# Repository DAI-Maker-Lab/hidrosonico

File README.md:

# Hidrosónico
<i>Hidrosónico</i> is a stream gauge using a <a href="http://www.maxbotix.com/documents/HRXL-MaxSonar-WR_Datasheet.pdf">MaxSonar HRXL MB7369</a> sonar rangefinder, a <a href="http://www.seeedstudio.com/wiki/Seeeduino-Stalker_v3">Seeeduino Stalker v3</a> Arduino-compatible microcontroller platform, and an <a href="https://learn.adafruit.com/adafruit-fona-mini-gsm-gprs-cellular-phone-module/overview">Adafruit FONA 800</a> GSM module. It reads the distance between the sensor (specifically from where the housing meets the threading) and the water's surface directly below and sends this data at specified intervals to cloud-based storage, SMS, and/or email as determined by the user. It was designed to aid in collection of hydrological data and for flood early warning in developing countries. This version integrates a rain gauge at the request of the recipient. 

The code provided sends data to data.sparkfun.com as the cloud service but it could be easily adapted to any other provider. Please note the places in the code that are marked for user-specific input.

This is a beta unit and we will be making changes as a result of the data and experiences we are collecting from pilot installations in Honduras, as well as feedback from on-the-ground partners like CODEM-DC in Tegucigalpa.

All code and hardware files are being made available under open source licensing. If you use it, please let us know (robert_ryan-silva[at]dai.com), and if you improve it, please share!

##Bill of Materials

Links to vendors are provided for convenience and not meant to imply an endorsement of that vendor; most of the items are available from other sources, and most components can be adequately substituted with equivalents. We have no connections nor receive any benefit from any of the vendors indicated.

###Required:
<ul>
<li><b><a href="http://www.seeedstudio.com/depot/Seeeduino-Stalker-v3-p-1882.html?cPath=6_7">Seeeduino Stalker v3</a></b>. Most Arduino-compatible microcontrollers will work, but most will require additional circuitry to charge the battery from a solar cell and for use of the real-time clock. Some Arduino-compatibles will require some pin changes (though the Arduino Uno and its equivalents should be fine).</li>
<li><b><a href="https://www.adafruit.com/products/1946">Adafruit FONA 800</a> and <a href="https://www.adafruit.com/products/1859">antenna</a></b>. The FONA 808 would also work, but would require some wiring changes and would not fit on the circuit board as designed. Any GSM module that is not based on the SIMCOM SIM 800 series chips would need code changes to work properly.</li>
<li><b><a href="http://www.amazon.com/Maxbotix-MB7369-HRXL-MaxSonar-WRM/dp/B00A7YHBT2/ref=sr_1_1?ie=UTF8&qid=1434393383&sr=8-1&keywords=Maxbotix+MaxSonar+HRXL+MB7369&pebp=1434393385707&perid=1H5KG4AJ9JRJ434Q8SGC">Maxbotix MaxSonar HRXL MB7369</a></b>.</li>
<li><b>A solar panel</b>. We use <a href="https://www.adafruit.com/products/500">these</a>. We have not found any panels that terminate in the JST connector that the Stalker takes, so a <a href="https://www.adafruit.com/products/261">JST connector</a> is highly recommended; <a href="http://www.amazon.com/gp/product/B0076AY6J8?psc=1&redirect=true&ref_=oh_aui_search_detailpage">Scotchlok butt connectors</a> or similar (inside the enclosure, of course) make connecting the JST connector to the solar panel quite easy.</li>
<li><b>A lithium-ion battery</b>. We use <a href="https://www.adafruit.com/products/1781">these</a>.</li>
</ul>

###Optional:
<ul>
<li><b>Rain gauge</b>. You can collect rainfall data at the same site for a minimal additional cost with the addition of a rain gauge. The <i>Hidrosónico</i> code in the repository records data from a simple <a href="https://www.argentdata.com/catalog/product_info.php?products_id=168">Argent Data Systems rain gauge</a>. You'll need two 1K ohm resistors and a pair of 1N148 diodes to wire it to the microcontroller; an RJ-11 jack <a href="https://www.sparkfun.com/products/132">like this one from Sparkfun</a> will make this easier to work with, but you could strip the wires and solder them directly.</li>
<li><b>Circuit board</b>. Eagle files for a custom circuit board to accommodate the FONA and the optional rain gauge are included in the repository. You could cut this on a CNC machine or have it fabricated by a vendor like <a href="https://oshpark.com/">OSH Park</a>. It isn't strictly necessary -- you could wire the FONA directly -- but we found in practice that installation can be a violent process and connections coming loose is a real possibility. It is recommended especially if you intend to implement the rain gauge.</li>
<li><b>Interior structure</b>. The repository includes a STL file for an interior frame to hold the various internal components stable inside a 4 x 4 x 2 inch PVC junction box <a href=http://www.homedepot.com/p/Carlon-4-in-x-4-in-x-2-in-PVC-Junction-Box-5-Pack-E989NNJ-CAR/202206114">like this one</a>. We cut a 1-inch hole in the faceplate of the junction box and use PVC cement to attach a threaded 3/4-inch coupling <a href="http://www.homedepot.com/p/Carlon-3-4-in-PVC-Coupling-E940E-CTN/100404040">like this one</a>. Again, it's not necessary, but it does keep things from banging around much during installation. Additional holes must be drilled to accommodate the solar panel and the rain gauge. We use plumber's putty to fill the gaps around the cabling.</li>
<li><b>Mounts</b>. You'll want to mount the solar panel and optional rain gauge somehow. The repository includes SVG files for mounts that we have used with the PVC junction boxes. We cut these from sheet metal using waterjet cutters or 3.5mm polypropylene using laser cutters; both have the advantage of being easily bendable (with heat, in the case of polypropylene) to the desired angle. For those without access to fancy CNC cutters, the repository also includes a template for a simpler sheet metal solar panel mount that could be cut with aviation shears or other sheet metal cutting implements.</li>
<li><b><a href="http://www.seeedstudio.com/depot/Grove-4-pin-Female-Jumper-to-Grove-4-pin-Conversion-Cable-5-PCs-per-PAck-p-1020.html?cPath=98_106_57">Grove <-> female jumper cable</a></b>. Makes connecting the MaxBotix to the Stalker very easy indeed.</li>
<li><b>An Xbee 802.15.4 radio</b> will allow you to reprogram the unit from nearby without physically opening the housing, which can be a serious hassle depending on where the unit is mounted.</li>

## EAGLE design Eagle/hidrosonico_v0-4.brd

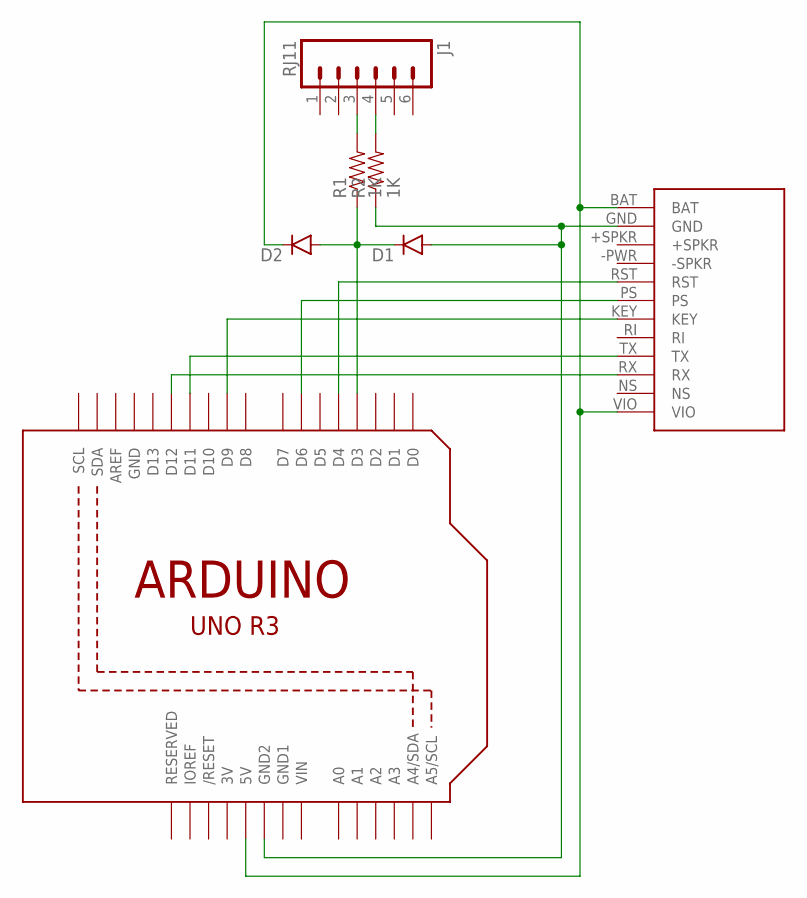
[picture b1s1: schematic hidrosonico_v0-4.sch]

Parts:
D1, D2: DIODE1N4148; DIODE-1N4148
J1: RJ11; RJ11-6
R1, R2: 1K; AXIAL-0.5
U2: ARDUINOR3-DIMENSION; ARDUINOR3
U$1: ADAFRUIT_FONA800; FONA

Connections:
3V: U2.3V
GND: D1.A, R2.P$1 (1), U2.GND, U2.GND2, U$1.GND
GND1: U2.GND1
unnamed: U2.D4, U$1.RST
unnamed: U2.D6, U$1.PS
unnamed: U2.D9, U$1.KEY
unnamed: U2.D11, U$1.TX
unnamed: U2.D12, U$1.RX
unnamed: J1.3, R1.P$2 (2)
unnamed: D1.C, D2.A, R1.P$1 (1), U2.D3
unnamed: J1.4, R2.P$2 (2)
VCC+: D2.C, U2.5V, U$1.BAT, U$1.VIO
VIN: U2.VIN

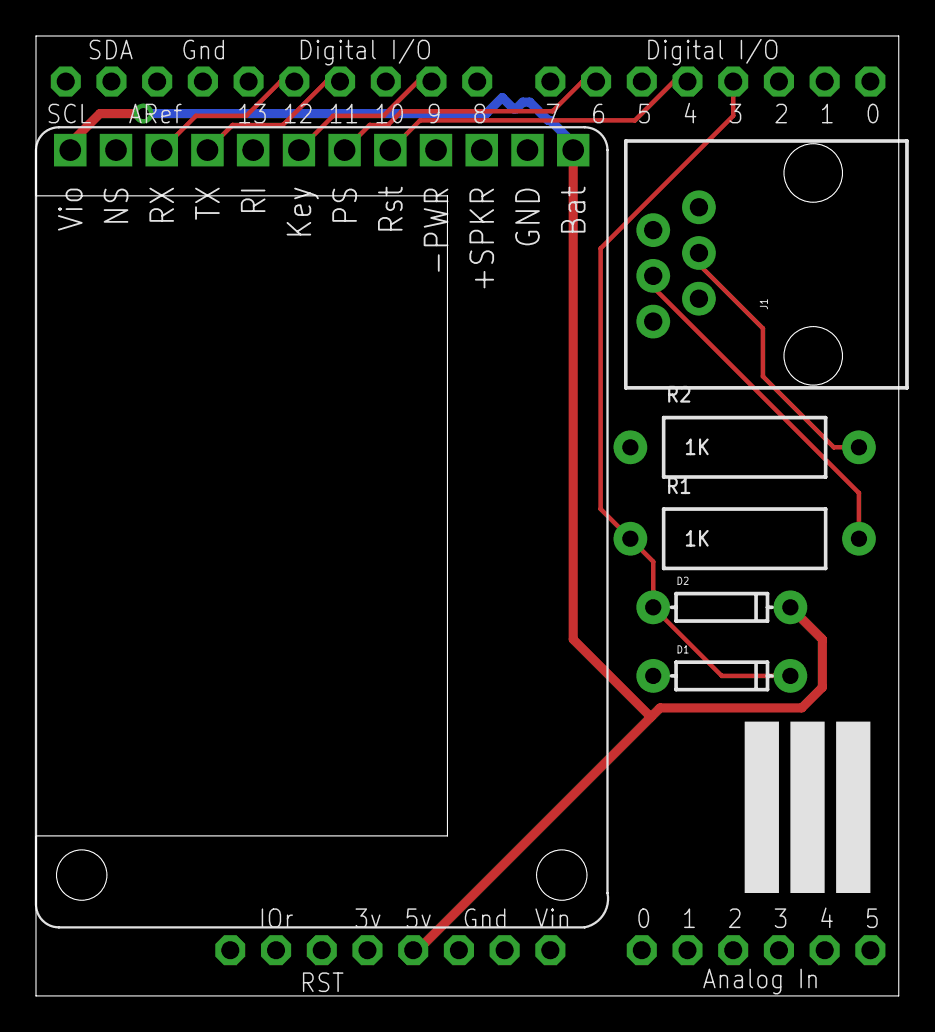
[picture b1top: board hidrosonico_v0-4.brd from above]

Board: 2 copper layers, 47.9 x 53.3 mm, 7 parts (0 on the bottom side), 10 nets.

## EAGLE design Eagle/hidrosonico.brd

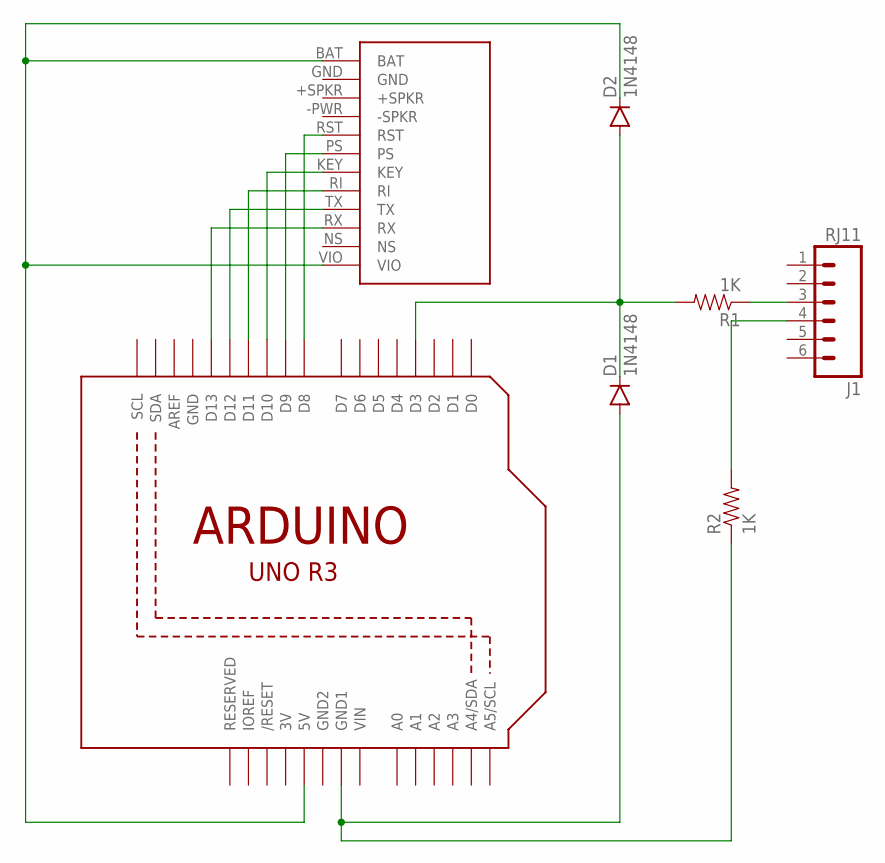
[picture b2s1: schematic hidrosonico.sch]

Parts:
D1, D2: 1N4148; DIODE-1N4148
J1: RJ11; RJ11-6
R1, R2: 1K; AXIAL-0.5
U1: ARDUINOR3-DIMENSION; ARDUINOR3
U$1: ADAFRUIT_FONA; FONA

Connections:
3V: U1.3V
GND: U1.GND, U$1.GND
GND2: U1.GND2
KEY: U1.D10, U$1.KEY
unnamed: U1.D9, U$1.PS
unnamed: J1.3, R1.P$1 (1)
unnamed: D1.A, R2.P$1 (1), U1.GND1
unnamed: D1.C, D2.A, R1.P$2 (2), U1.D3
unnamed: J1.4, R2.P$2 (2)
PWR: D2.C, U1.5V, U$1.BAT, U$1.VIO
RI: U1.D11, U$1.RI
RST: U1.D8, U$1.RST
RX: U1.D13, U$1.RX
TX: U1.D12, U$1.TX
VIN: U1.VIN

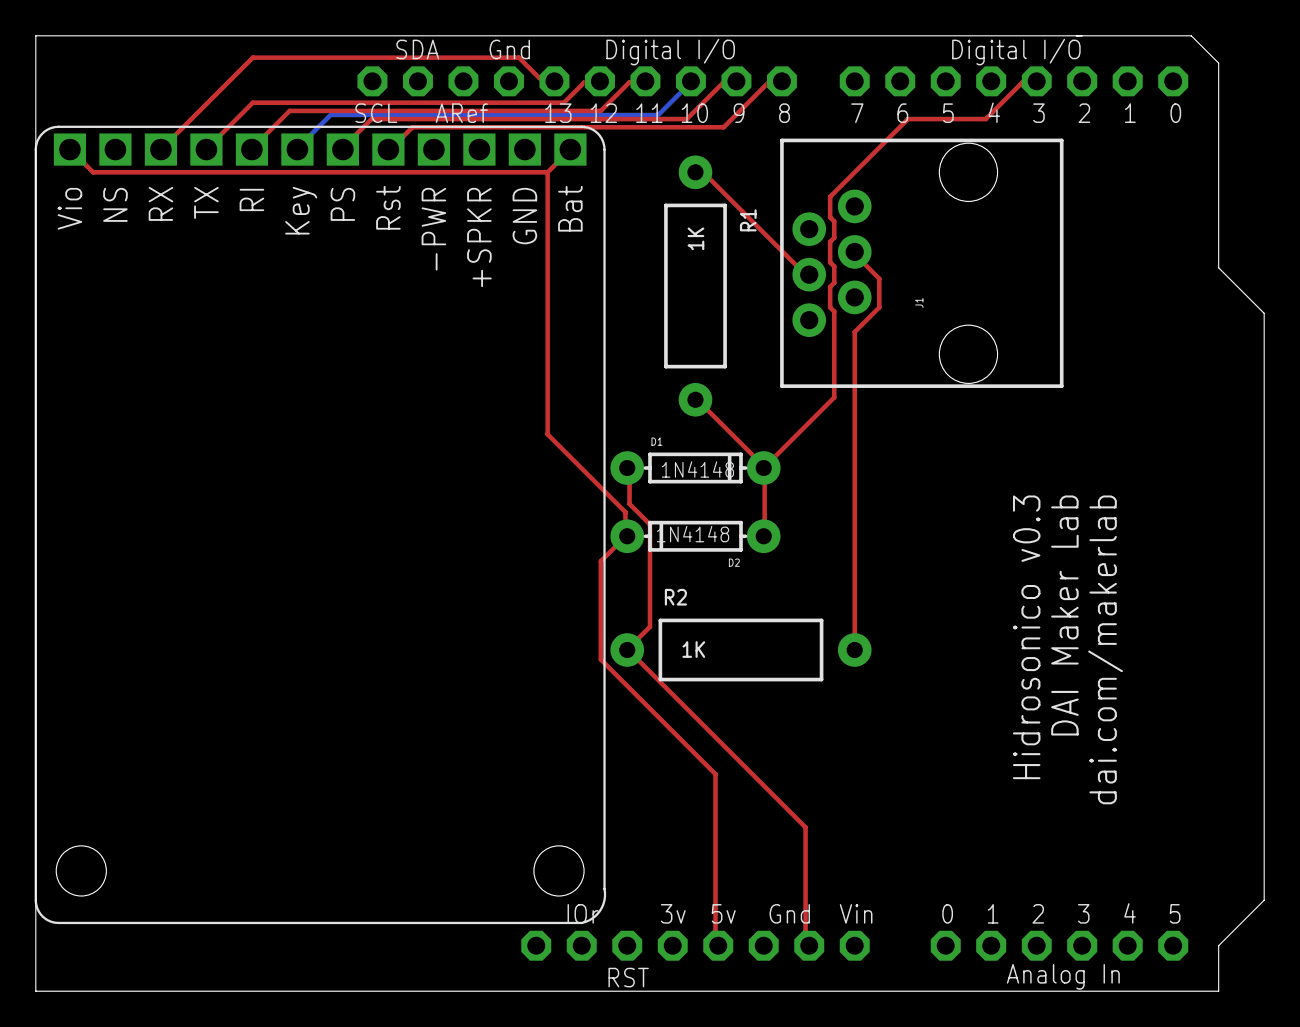
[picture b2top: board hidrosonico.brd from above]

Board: 2 copper layers, 68.6 x 53.3 mm, 7 parts (0 on the bottom side), 12 nets.

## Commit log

2015-06-26 Create LICENSE
2015-06-26 Add non-text files to repository
2015-07-07 Update hidrosonico.ino
    Implement changes resulting from pilot installation feedback: improved clockSet(), streamHeight-dependent message scheduling logic, negative streamHeight filtering, and reduced SRAM usage.
2015-09-18 Update hidrosonico.ino
    Update of Hidrosónico to v0.4. Changes include support for Xbee remote programming and increased reliability, particularly with regard to setting the RTC time.
2015-09-18 Updated Eagle board file
    Improved PCB design includes easier access to SIM slot on FONA and
    battery and solar jacks on Stalker.
2015-09-18 Added Bill of Materials

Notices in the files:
parts and their libraries:
SparkFun-Connectors: Licensing: Creative Commons ShareAlike 4.0 International - https://creativecommons.org/licenses/by-sa/4.0
